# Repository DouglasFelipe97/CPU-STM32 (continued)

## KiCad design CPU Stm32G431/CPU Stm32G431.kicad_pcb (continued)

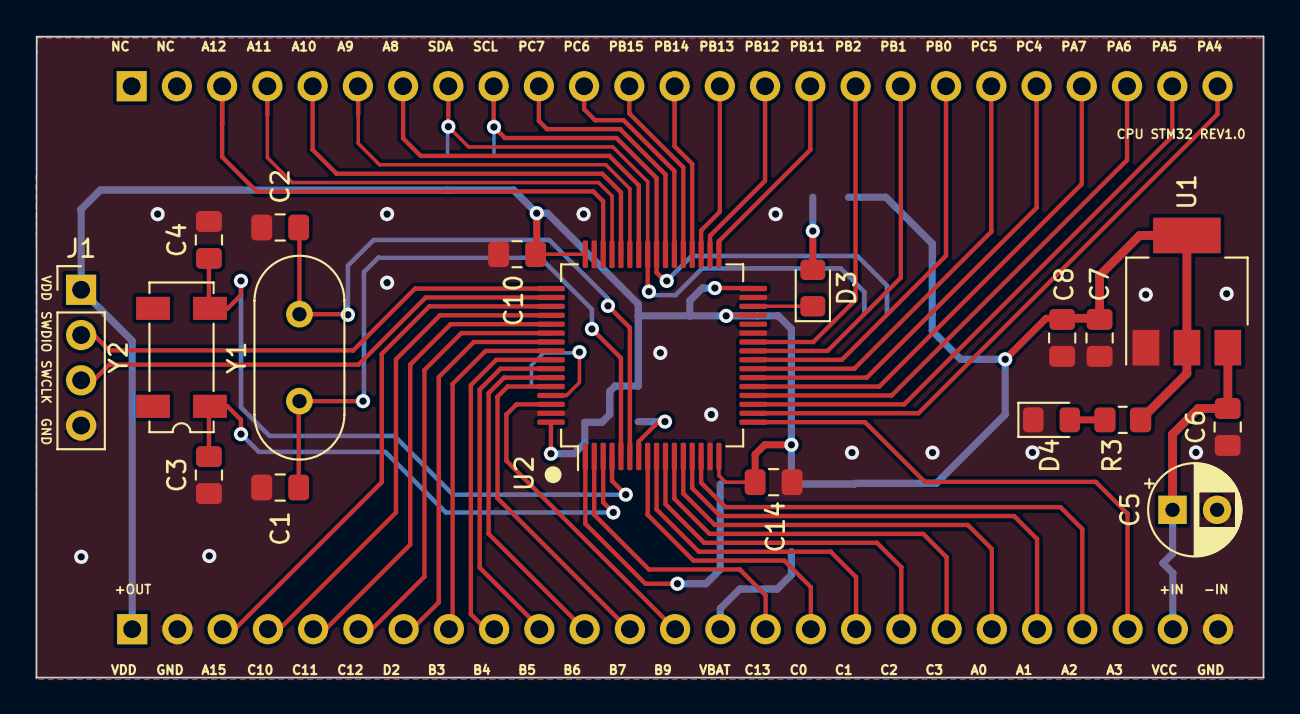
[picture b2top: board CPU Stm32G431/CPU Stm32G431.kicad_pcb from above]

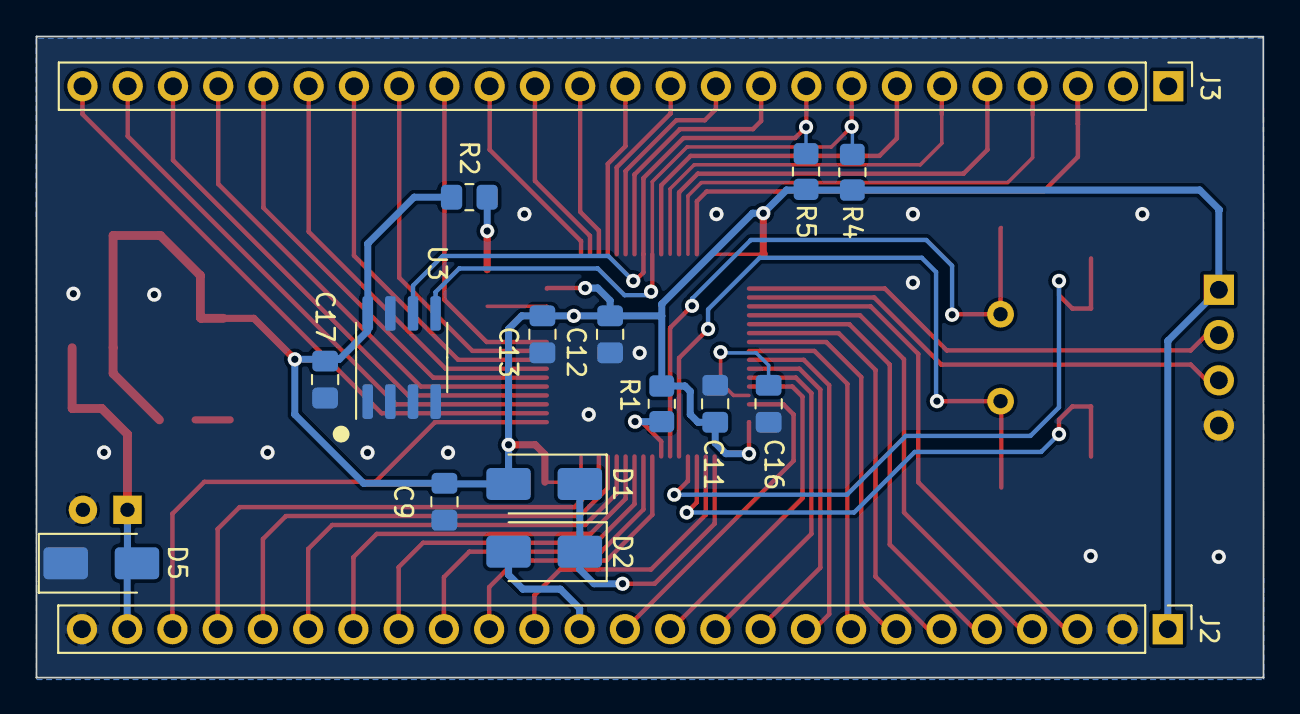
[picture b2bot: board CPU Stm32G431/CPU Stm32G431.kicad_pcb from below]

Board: 2 copper layers, 68.9 x 36.0 mm, 34 parts (16 on the bottom side), 59 nets.
